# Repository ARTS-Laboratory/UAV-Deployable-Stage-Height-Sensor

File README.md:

# UAV-Deployable-Stage-Height-Sensor
UAV Deployable Stage Height Sensor with Electro-permanent Magnet Docking Mechanism

<p align="center">
Figure 1: Drone delivering a sensor package underneath a structure.
</p>

## V0
1. Data logging saved onto SD card
2. Battery monitoring
3. Solar load sharing
4. Measures stage, temperature, pressure, humidity
5. EPM with wireless toggling to attach under structures

## V1 (projected)
1. Adaptive sampling algorithm
2. Wireless data transfer with GUI
3. Camera integration

## Licensing and Citation

[![CC BY-SA 4.0][cc-by-sa-shield]][cc-by-sa]

This work is licensed under a
[Creative Commons Attribution-ShareAlike 4.0 International License][cc-by-sa].

[cc-by-sa]: http://creativecommons.org/licenses/by-sa/4.0/
[cc-by-sa-image]: https://licensebuttons.net/l/by-sa/4.0/88x31.png
[cc-by-sa-shield]: https://img.shields.io/badge/License-CC%20BY--SA%204.0-lightgrey.svg

Cite as:

@Misc{ARTSLabUavDeployableStage,     
  author = {{ARTS-L}ab},  
  howpublished = {GitHub},  
  title  = {{UAV} Deployable Stage Height Sensor}, 
  groups = {{ARTS-L}ab},    
  url    = {https://github.com/ARTS-Laboratory/UAV-Deployable-Stage-Height-Sensor},   
}

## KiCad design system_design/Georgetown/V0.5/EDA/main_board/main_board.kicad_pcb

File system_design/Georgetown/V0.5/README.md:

# UAV Rapidly-Deployable Stage Sensor with Permanent Magnet Docking Mechanism for Flood Monitoring in Undersampled Watersheds

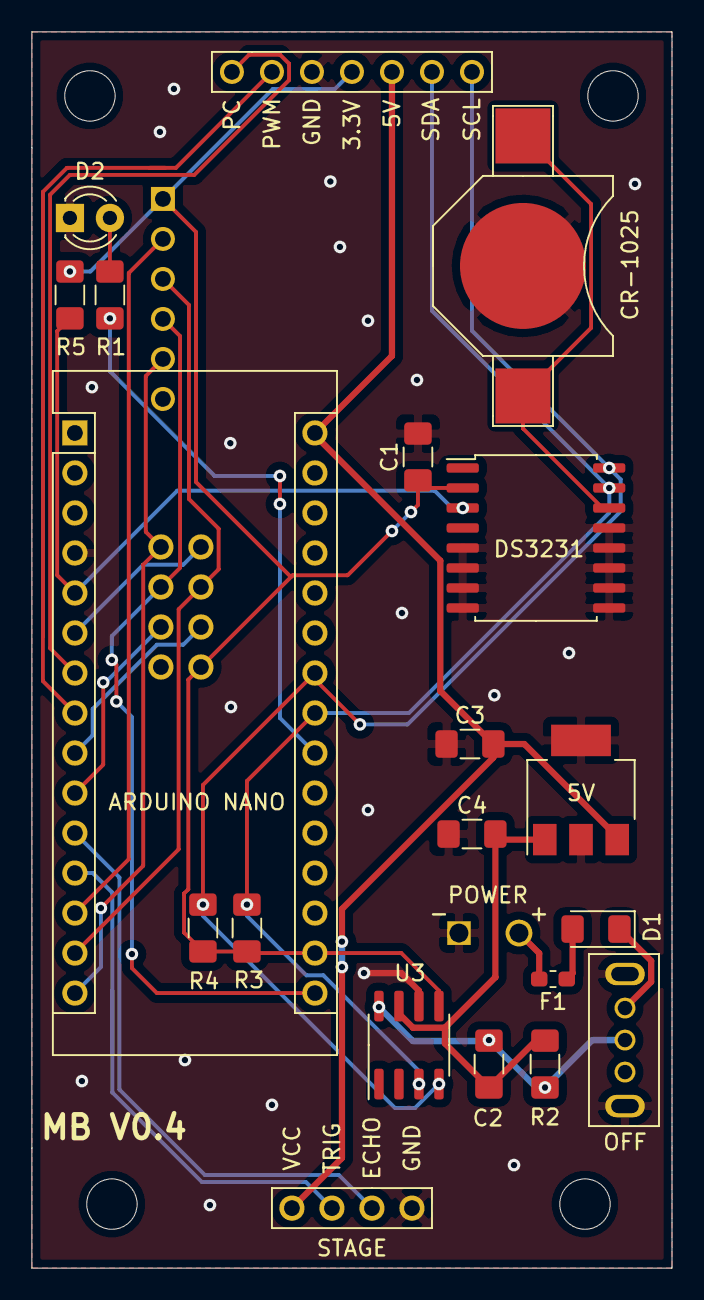
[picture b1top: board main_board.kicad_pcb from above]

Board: 2 copper layers, 40.6 x 78.5 mm, 23 parts (0 on the bottom side), 25 nets.

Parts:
5V: KA78M05_TO252; SOT-223-3_TabPin2
ARDUINO NANO: Arduino_Nano_v2.x-MCU_Module; Arduino_Nano
C1, C2, C3, C4: C; C_1206_3216Metric_Pad1.42x1.75mm_HandSolder
CR-1025: Battery_Cell; battery_holder_10mm
D1: D; D_1206_3216Metric_Pad1.42x1.75mm_HandSolder
D2: LED; LED_D3.0mm
DS3231: DS3231M; SOIC-16W_7.5x10.3mm_P1.27mm
F1: Fuse; R_0603_1608Metric_Pad1.05x0.95mm_HandSolder
MICRO SD: small_microSD; small_microSD_v2
POWER: XP60PW; XT60PW
R1: 1k; C_1206_3216Metric_Pad1.42x1.75mm_HandSolder
R2: Rs; R_1206_3216Metric_Pad1.42x1.75mm_HandSolder
R3, R4: 4.7k; C_1206_3216Metric_Pad1.42x1.75mm_HandSolder
R5: 4.7k; R_1206_3216Metric_Pad1.42x1.75mm_HandSolder
STAGE: HCSR04
U1: top_rail_v2
U3: INA219AxD; SOIC-8_3.9x4.9mm_P1.27mm
nRF24L01+1: nRF24L01+
switch1: grounded_switch

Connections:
GND: 5V.2, ARDUINO NANO.4, ARDUINO NANO.29, C1.2, C3.1, C4.1, CR-1025.2, D2.1, DS3231.5, DS3231.6, DS3231.7, DS3231.8, DS3231.9, DS3231.10, DS3231.11, DS3231.12, DS3231.13, MICRO SD.6, POWER.1, STAGE.1, U1.6, U3.6, nRF24L01+1.5, switch1.4, switch1.5
unnamed: ARDUINO NANO.5, DS3231.3, R5.1
unnamed: ARDUINO NANO.6, nRF24L01+1.4
unnamed: ARDUINO NANO.7, U1.8
unnamed: ARDUINO NANO.8, U1.7
unnamed: ARDUINO NANO.9, nRF24L01+1.2
unnamed: ARDUINO NANO.10, nRF24L01+1.6
unnamed: ARDUINO NANO.11, STAGE.2
unnamed: ARDUINO NANO.12, STAGE.3
unnamed: ARDUINO NANO.13, MICRO SD.2
unnamed: ARDUINO NANO.14, MICRO SD.3, nRF24L01+1.3
unnamed: ARDUINO NANO.15, MICRO SD.5, nRF24L01+1.8
unnamed: ARDUINO NANO.16, MICRO SD.4, nRF24L01+1.7
unnamed: ARDUINO NANO.17, C1.1, DS3231.2, MICRO SD.1, R3.1, R4.1, R5.2, U1.5, U3.5, nRF24L01+1.1
unnamed: ARDUINO NANO.22, R1.1
unnamed: ARDUINO NANO.23, DS3231.15, R3.2, U1.3, U3.3
unnamed: ARDUINO NANO.24, DS3231.16, R4.2, U1.2, U3.4
unnamed: 5V.3, ARDUINO NANO.30, C3.2, STAGE.4, U1.4
unnamed: CR-1025.1, DS3231.14
unnamed: C2.1, R2.1, U3.8, switch1.2
unnamed: 5V.1, C2.2, C4.2, R2.2, U3.7
unnamed: D1.1, switch1.1
unnamed: D1.2, F1.1
unnamed: D2.2, R1.2
unnamed: F1.2, POWER.2

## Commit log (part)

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2021-12-16 moving things around
2021-12-16 add images
2021-12-29 add CAD files
2021-12-31 update data collection sketch
2022-01-16 change CE, CSN in rf_controller.ino
2022-01-20 refill PCB zones
2022-02-10 update most recent footprints
2022-02-12 adjust alarm logic
2022-02-12 major cleanup
2022-02-16 update interrupt pin syntax
2022-02-18 add svg files
2022-02-18 add pdf figures
    font is embedded
2022-02-18 Revert "add svg files"
    This reverts commit 7ab9268956233aa73e6df829ee35e90687d1be37.
2022-02-18 Revert "Revert "add svg files""
    This reverts commit 5661a4fa033972c015758a2f4f67f32fc668bec8.
2022-02-18 add figure data
2022-02-19 add bill of materials
2022-02-19 modify serial printed sketch name
2022-02-19 add f3d files
2022-02-19 change pdf_figures file name
2022-02-19 add graphical_abstract.png
2022-02-25 add libraries
2022-05-23 change SD file name, fix mag_msg issue
2022-05-23 change SD file name
2022-05-30 updated citation
2022-05-31 update all figures
2025-02-06 added variations
2025-02-24 New Sensor Housing Design
2025-02-24 Data Collection Code (unfinished)
2025-02-25 code updates
2025-02-26 V0.5 added
2025-02-27 updated to latest KiCAD version
2025-02-28 Update BOM
2026-06-16 OS 0.5.2 added
2026-06-17 added a .0 to a major version number.
